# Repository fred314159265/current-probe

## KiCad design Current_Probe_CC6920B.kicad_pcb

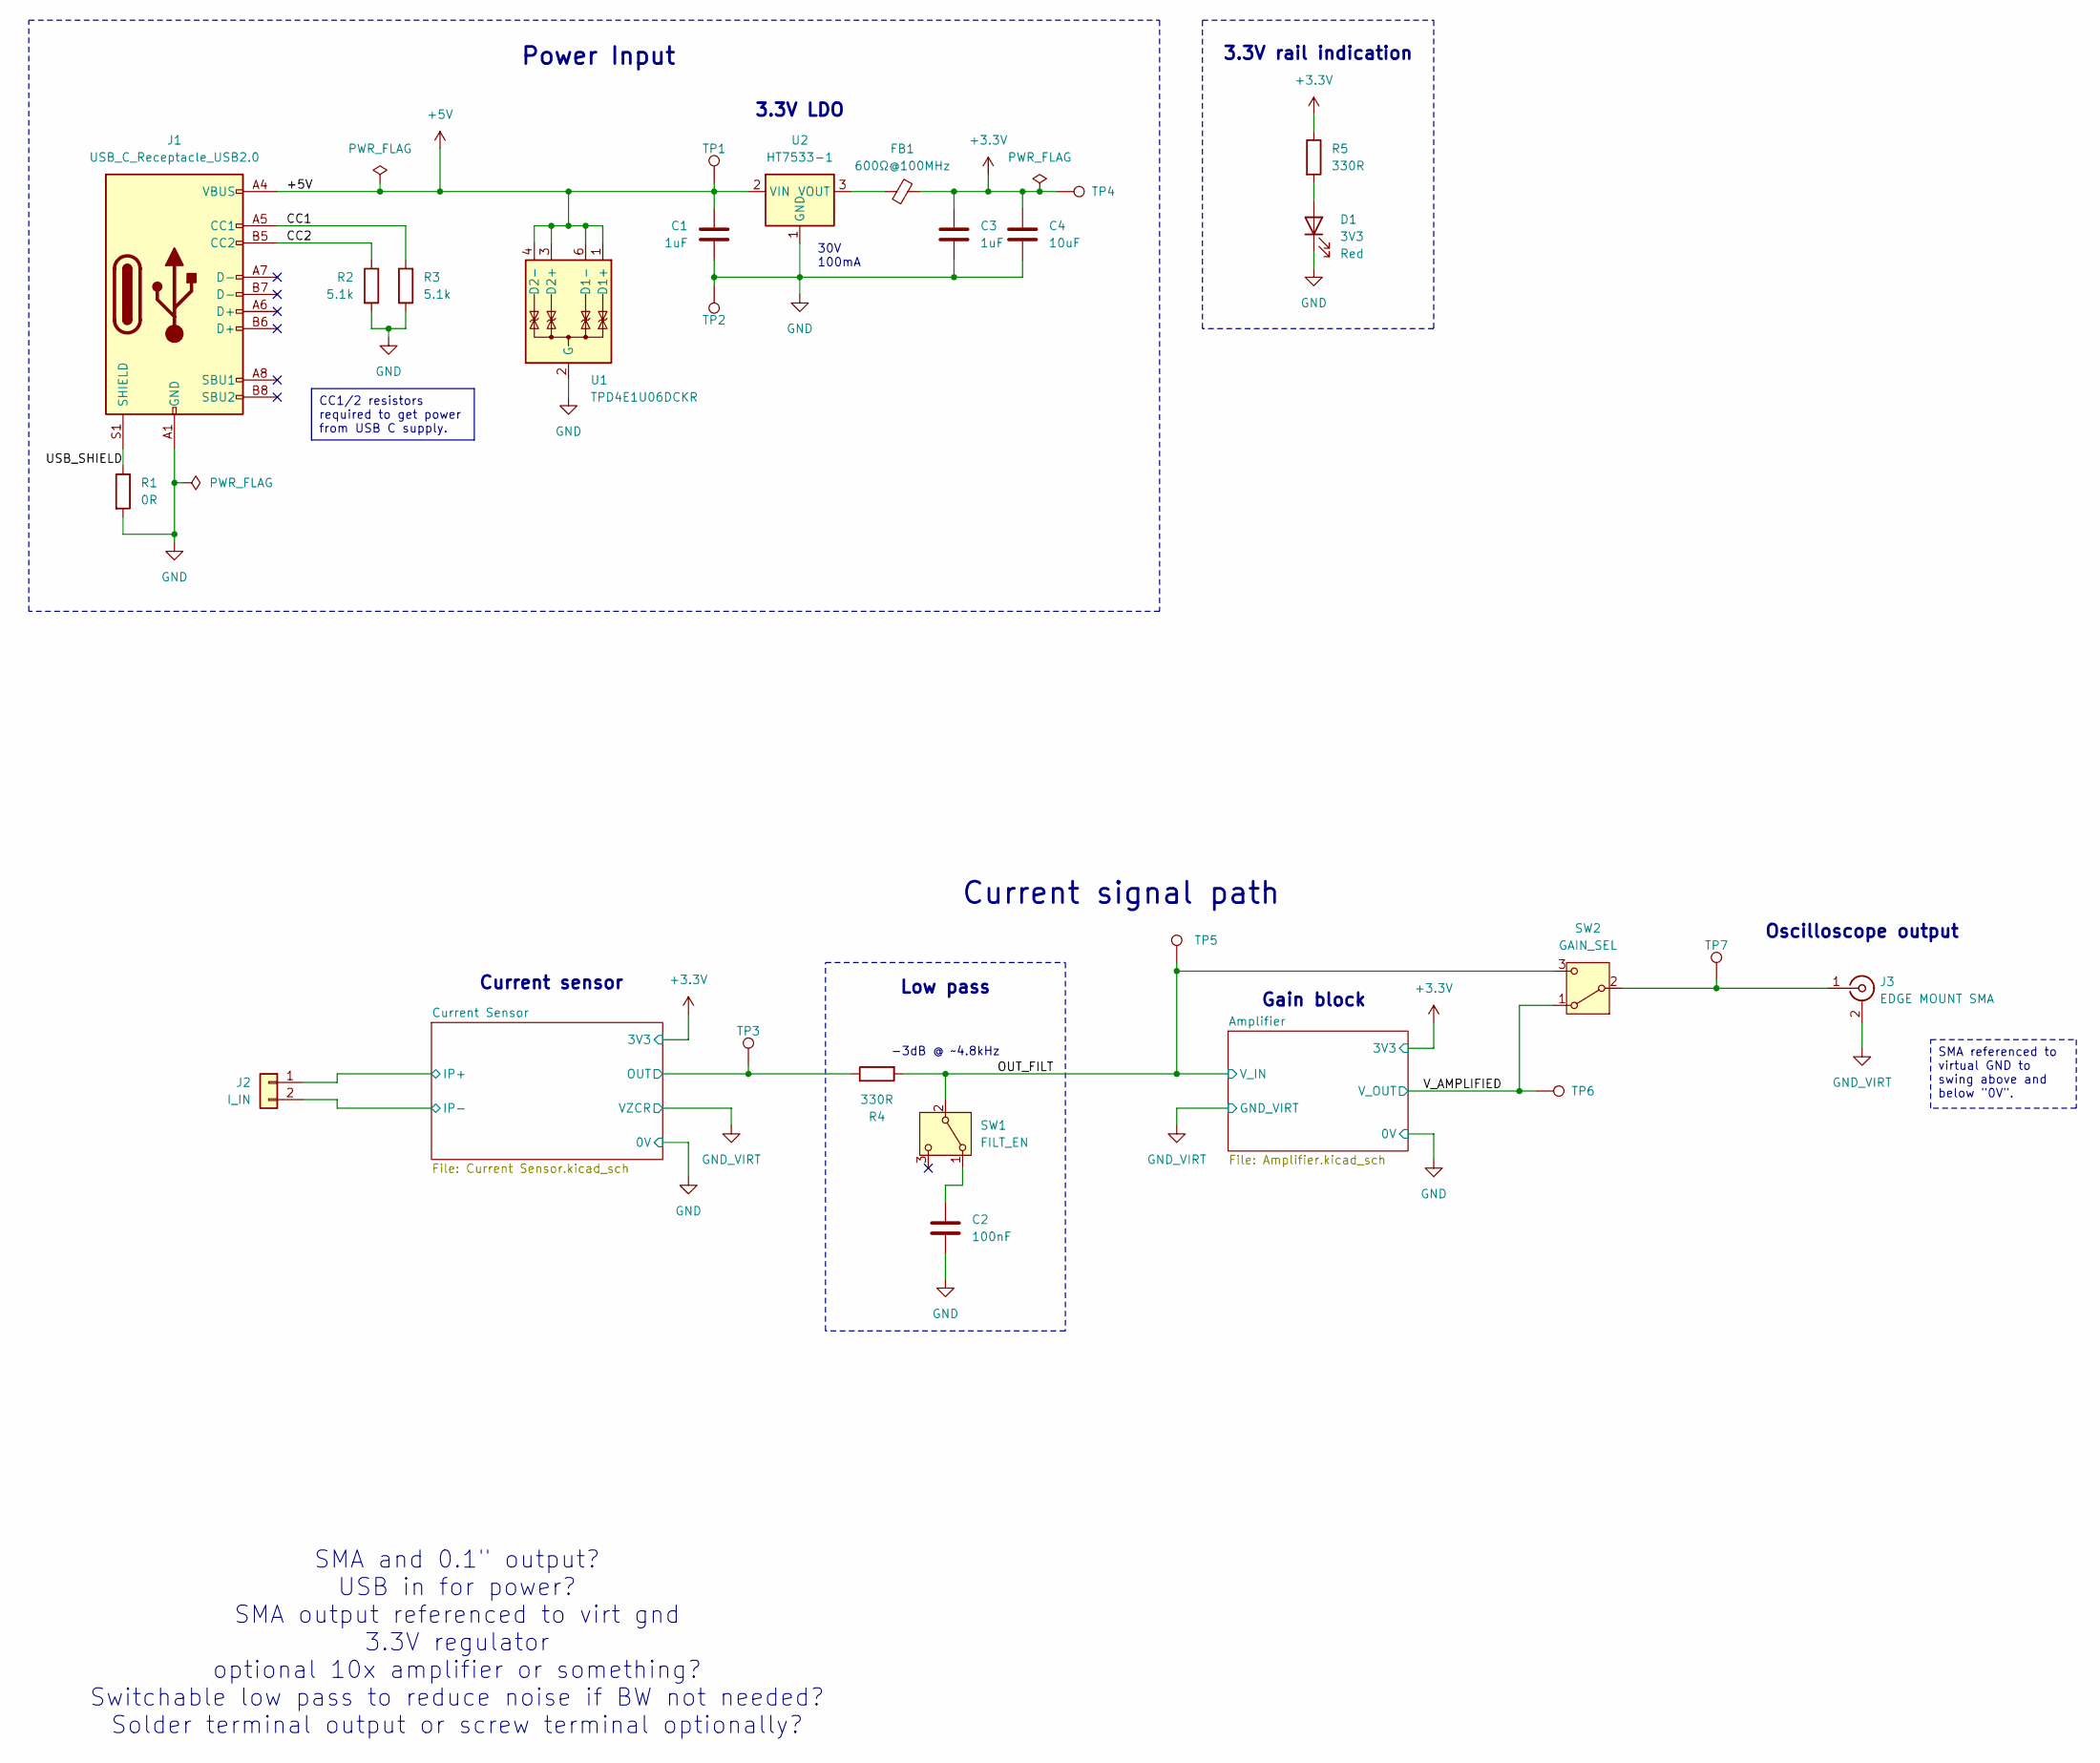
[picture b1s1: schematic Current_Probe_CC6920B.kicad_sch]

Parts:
C1, C3: 1uF; C_0805_2012Metric; Manufacturer Part # CL21B105KBFNNNE; LCSC Part # C28323
C2: 100nF; C_0603_1608Metric; Manufacturer Part # CC0603KRX7R9BB104; LCSC Part # C14663
C4: 10uF; C_0603_1608Metric; Manufacturer Part # CL10A106MA8NRNC; LCSC Part # C96446
D1: 3V3; LED_0603_1608Metric; Manufacturer Part # KT-0603R; LCSC Part # C2286
FB1: 600Ω@100MHz; L_0603_1608Metric; Manufacturer Part # GZ1608D601TF; LCSC Part # C1002
J1: USB_C_Receptacle_USB2.0; USB_C_Receptacle_XKB_U262-16XN-4BVC11; Manufacturer Part # U262-161N-4BVC11; LCSC Part # C319148
J2: I_IN; TerminalBlock_Phoenix_MKDS-1,5-2_1x02_P5.00mm_Horizontal; Manufacturer Part # WJ128V-5.0-2P; LCSC Part # C8269
J3: EDGE MOUNT SMA; SMA_Samtec_SMA-J-P-H-ST-EM1_EdgeMount; Manufacturer Part # BWSMA-KE-P001; LCSC Part # C496550
R1: 0R; R_0603_1608Metric; Manufacturer Part # 0603WAF0000T5E; LCSC Part # C21189
R2, R3: 5.1k; R_0603_1608Metric; Manufacturer Part # 0603WAF5101T5E; LCSC Part # C23186
R4, R5: 330R; R_0603_1608Metric; Manufacturer Part # 0603WAF3300T5E; LCSC Part # C23138
SW1: FILT_EN; SW_SPDT_PCM12; Manufacturer Part # SSSS811101; LCSC Part # C109335
SW2: GAIN_SEL; SW_SPDT_PCM12; Manufacturer Part # SSSS811101; LCSC Part # C109335
TP1, TP2, TP3, TP4, TP5, TP6, TP7: TestPoint; TestPoint_THTPad_1.0x1.0mm_Drill0.5mm
U1: TPD4E1U06DCKR; SOT-363_SC-70-6; LCSC Part # C194628
U2: HT7533-1; SOT-89-3; Manufacturer Part # HT7533-1; LCSC Part # C14289

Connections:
+3.3V: C3.1, C4.1, FB1.2, R5.1, TP4.1; also elsewhere on the board
+5V: C1.1, J1.A4 (VBUS), J1.A9 (VBUS), J1.B4 (VBUS), J1.B9 (VBUS), TP1.1, U1.1 (D1+), U1.3 (D2+), U1.4 (D2-), U1.6 (D1-), U2.2 (VIN)
/CC1: J1.A5 (CC1), R3.1
/CC2: J1.B5 (CC2), R2.1
/Current Sensor/IP+: J2.1; also elsewhere on the board
/Current Sensor/IP-: J2.2; also elsewhere on the board
/Current Sensor/OUT: R4.1, TP3.1; also elsewhere on the board
/OUT_FILT: R4.2, SW1.2 (B), SW2.3 (C), TP5.1; also elsewhere on the board
/USB_SHIELD: J1.S1 (SHIELD), R1.1
/V_AMPLIFIED: SW2.1 (A), TP6.1; also elsewhere on the board
GND: C1.2, C2.2, C3.2, C4.2, D1.1 (K), J1.A1 (GND), J1.A12 (GND), J1.B1 (GND), J1.B12 (GND), R1.2, R2.2, R3.2, TP2.1, U1.2 (G), U2.1 (GND); also elsewhere on the board
GND_VIRT: J3.2 (Ext); also elsewhere on the board
unnamed: D1.2 (A), R5.2
unnamed: J3.1 (In), SW2.2 (B), TP7.1
unnamed: C2.1, SW1.1 (A)
unnamed: FB1.1, U2.3 (VOUT)

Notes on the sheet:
CC1/2 resistors required to get power from USB C supply.
SMA referenced to virtual GND to swing above and below "0V".
30V 100mA
3.3V LDO
-3dB @ ~4.8kHz
Oscilloscope output
Low pass
3.3V rail indication
Power Input
SMA and 0.1" output? USB in for power? SMA output referenced to virt gnd 3.3V regulator optional 10x amplifier or something? Switchable low pass to reduce noise if BW not needed? Solder terminal output or screw terminal optionally?
Current sensor
Current signal path
Gain block

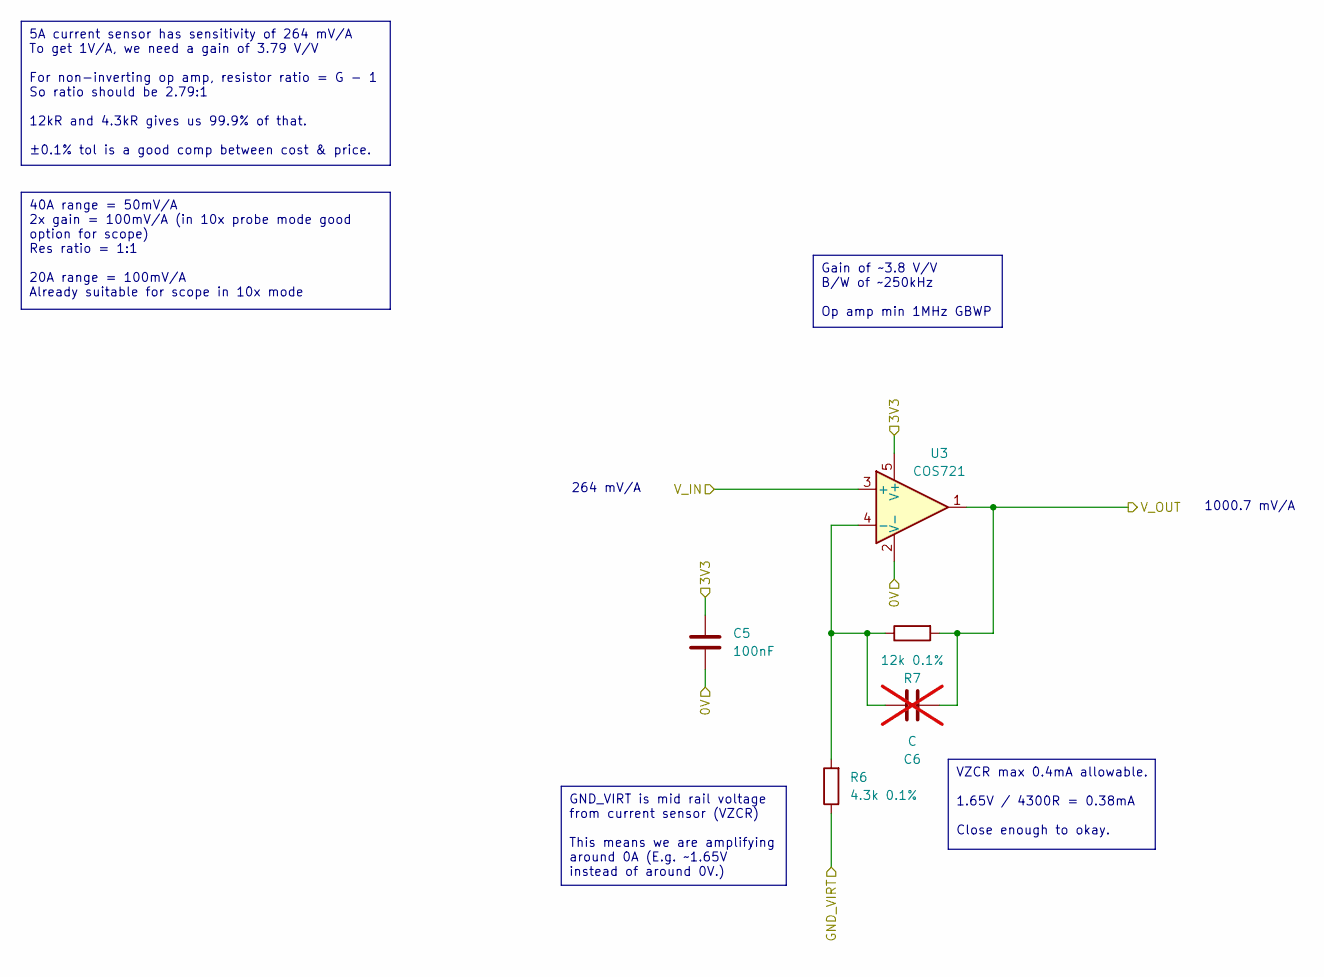
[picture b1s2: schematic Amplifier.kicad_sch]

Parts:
C5: 100nF; C_0603_1608Metric; Manufacturer Part # CC0603KRX7R9BB104; LCSC Part # C14663
C6: C; C_0603_1608Metric; not fitted
R6: 4.3k 0.1%; R_0603_1608Metric; Manufacturer Part # TD03G4301BT; LCSC Part # C666992
R7: 12k 0.1%; R_0603_1608Metric; Manufacturer Part # RT0603BRD0712KL; LCSC Part # C326735
U3: COS721; SOT-23-5; Manufacturer Part # COS721TR; LCSC Part # C693056

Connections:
+3.3V: C5.1, U3.5 (V+); also elsewhere on the board
/OUT_FILT: U3.3 (+); also elsewhere on the board
/V_AMPLIFIED: C6.2, R7.2, U3.1; also elsewhere on the board
GND: C5.2, U3.2 (V-); also elsewhere on the board
GND_VIRT: R6.1; also elsewhere on the board
unnamed: C6.1, R6.2, R7.1, U3.4 (-)

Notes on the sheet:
Gain of ~3.8 V/V B/W of ~250kHz Op amp min 1MHz GBWP
5A current sensor has sensitivity of 264 mV/A To get 1V/A, we need a gain of 3.79 V/V For non-inverting op amp, resistor ratio = G - 1 So ratio should be 2.79:1 12kR and 4.3kR gives us 99.9% of that. ±0.1% tol is a good comp between cost & price.
VZCR max 0.4mA allowable. 1.65V / 4300R = 0.38mA Close enough to okay.
GND_VIRT is mid rail voltage from current sensor (VZCR) This means we are amplifying around 0A (E.g. ~1.65V instead of around 0V.)
40A range = 50mV/A 2x gain = 100mV/A (in 10x probe mode good option for scope) Res ratio = 1:1 20A range = 100mV/A Already suitable for scope in 10x mode
264 mV/A
1000.7 mV/A

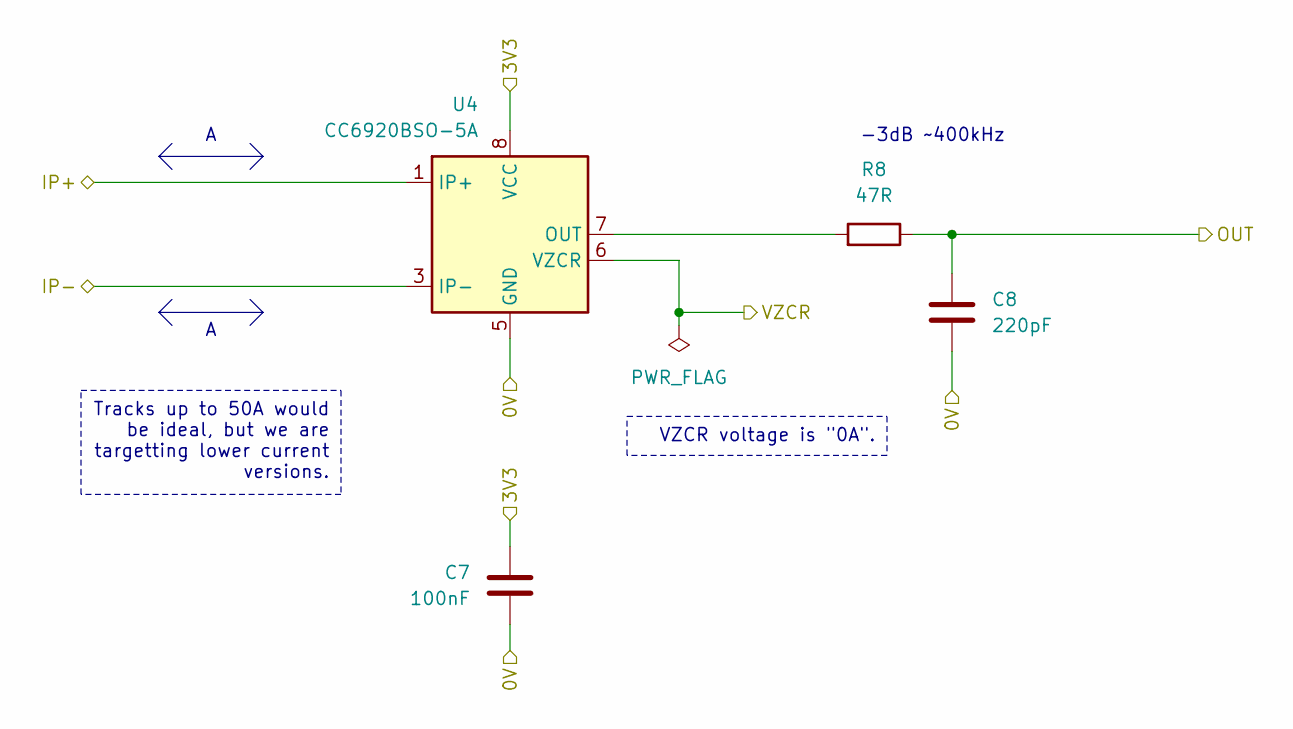
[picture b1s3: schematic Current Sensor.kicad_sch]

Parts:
C7: 100nF; C_0603_1608Metric; Manufacturer Part # CC0603KRX7R9BB104; LCSC Part # C14663
C8: 220pF; C_0603_1608Metric; Manufacturer Part # CL10B221KB8NNNC; LCSC Part # C1603
R8: 47R; R_0603_1608Metric; Manufacturer Part # 0603WAF470JT5E; LCSC Part # C23182
U4: CC6920BSO-5A; SOIC-8_3.9x4.9mm_P1.27mm; Manufacturer Part # CC6920BSO-5A; LCSC Part # C2880430

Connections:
+3.3V: C7.1, U4.8 (VCC); also elsewhere on the board
/Current Sensor/IP+: U4.1 (IP+), U4.2 (IP+); also elsewhere on the board
/Current Sensor/IP-: U4.3 (IP-), U4.4 (IP-); also elsewhere on the board
/Current Sensor/OUT: C8.1, R8.1; also elsewhere on the board
GND: C7.2, C8.2, U4.5 (GND); also elsewhere on the board
GND_VIRT: U4.6 (VZCR); also elsewhere on the board
unnamed: R8.2, U4.7 (OUT)

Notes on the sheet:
VZCR voltage is "0A".
Tracks up to 50A would be ideal, but we are targetting lower current versions.
-3dB ~400kHz

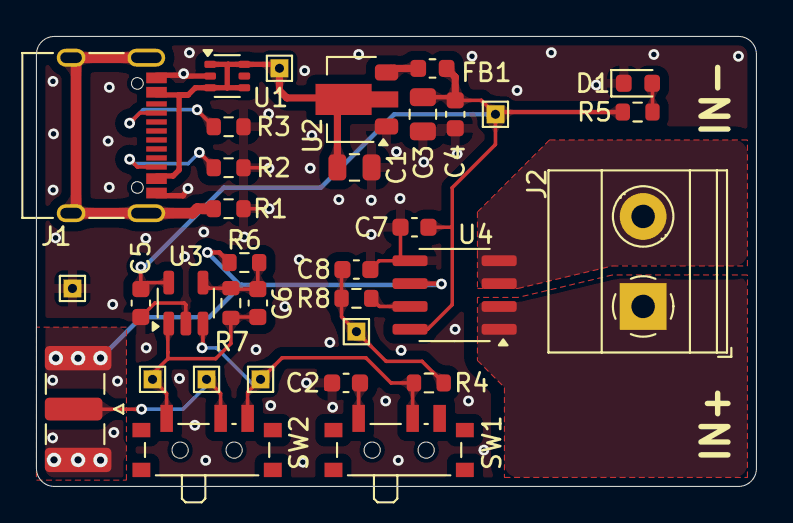
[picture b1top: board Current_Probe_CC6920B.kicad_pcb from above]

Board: 2 copper layers, 40.0 x 25.0 mm, 34 parts (0 on the bottom side), 18 nets.

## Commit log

2024-09-25 Started work on the design.
2024-09-26 Schematic mostly done?
2024-09-28 Working on the layout
2024-10-12 Rev A sent for manufacture.
